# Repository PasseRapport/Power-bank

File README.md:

# Power-bank

The objective of this project is to upcycle an old flashlight into a usb C power bank while conserving the original look and functionnality.

It is based on the IP2368 charge controller wich allow for dual mode Power Delivery charging up to 100W. However this board is designed to to supply 45w max (5 Amps at 9 Volts).

<br>

<br>

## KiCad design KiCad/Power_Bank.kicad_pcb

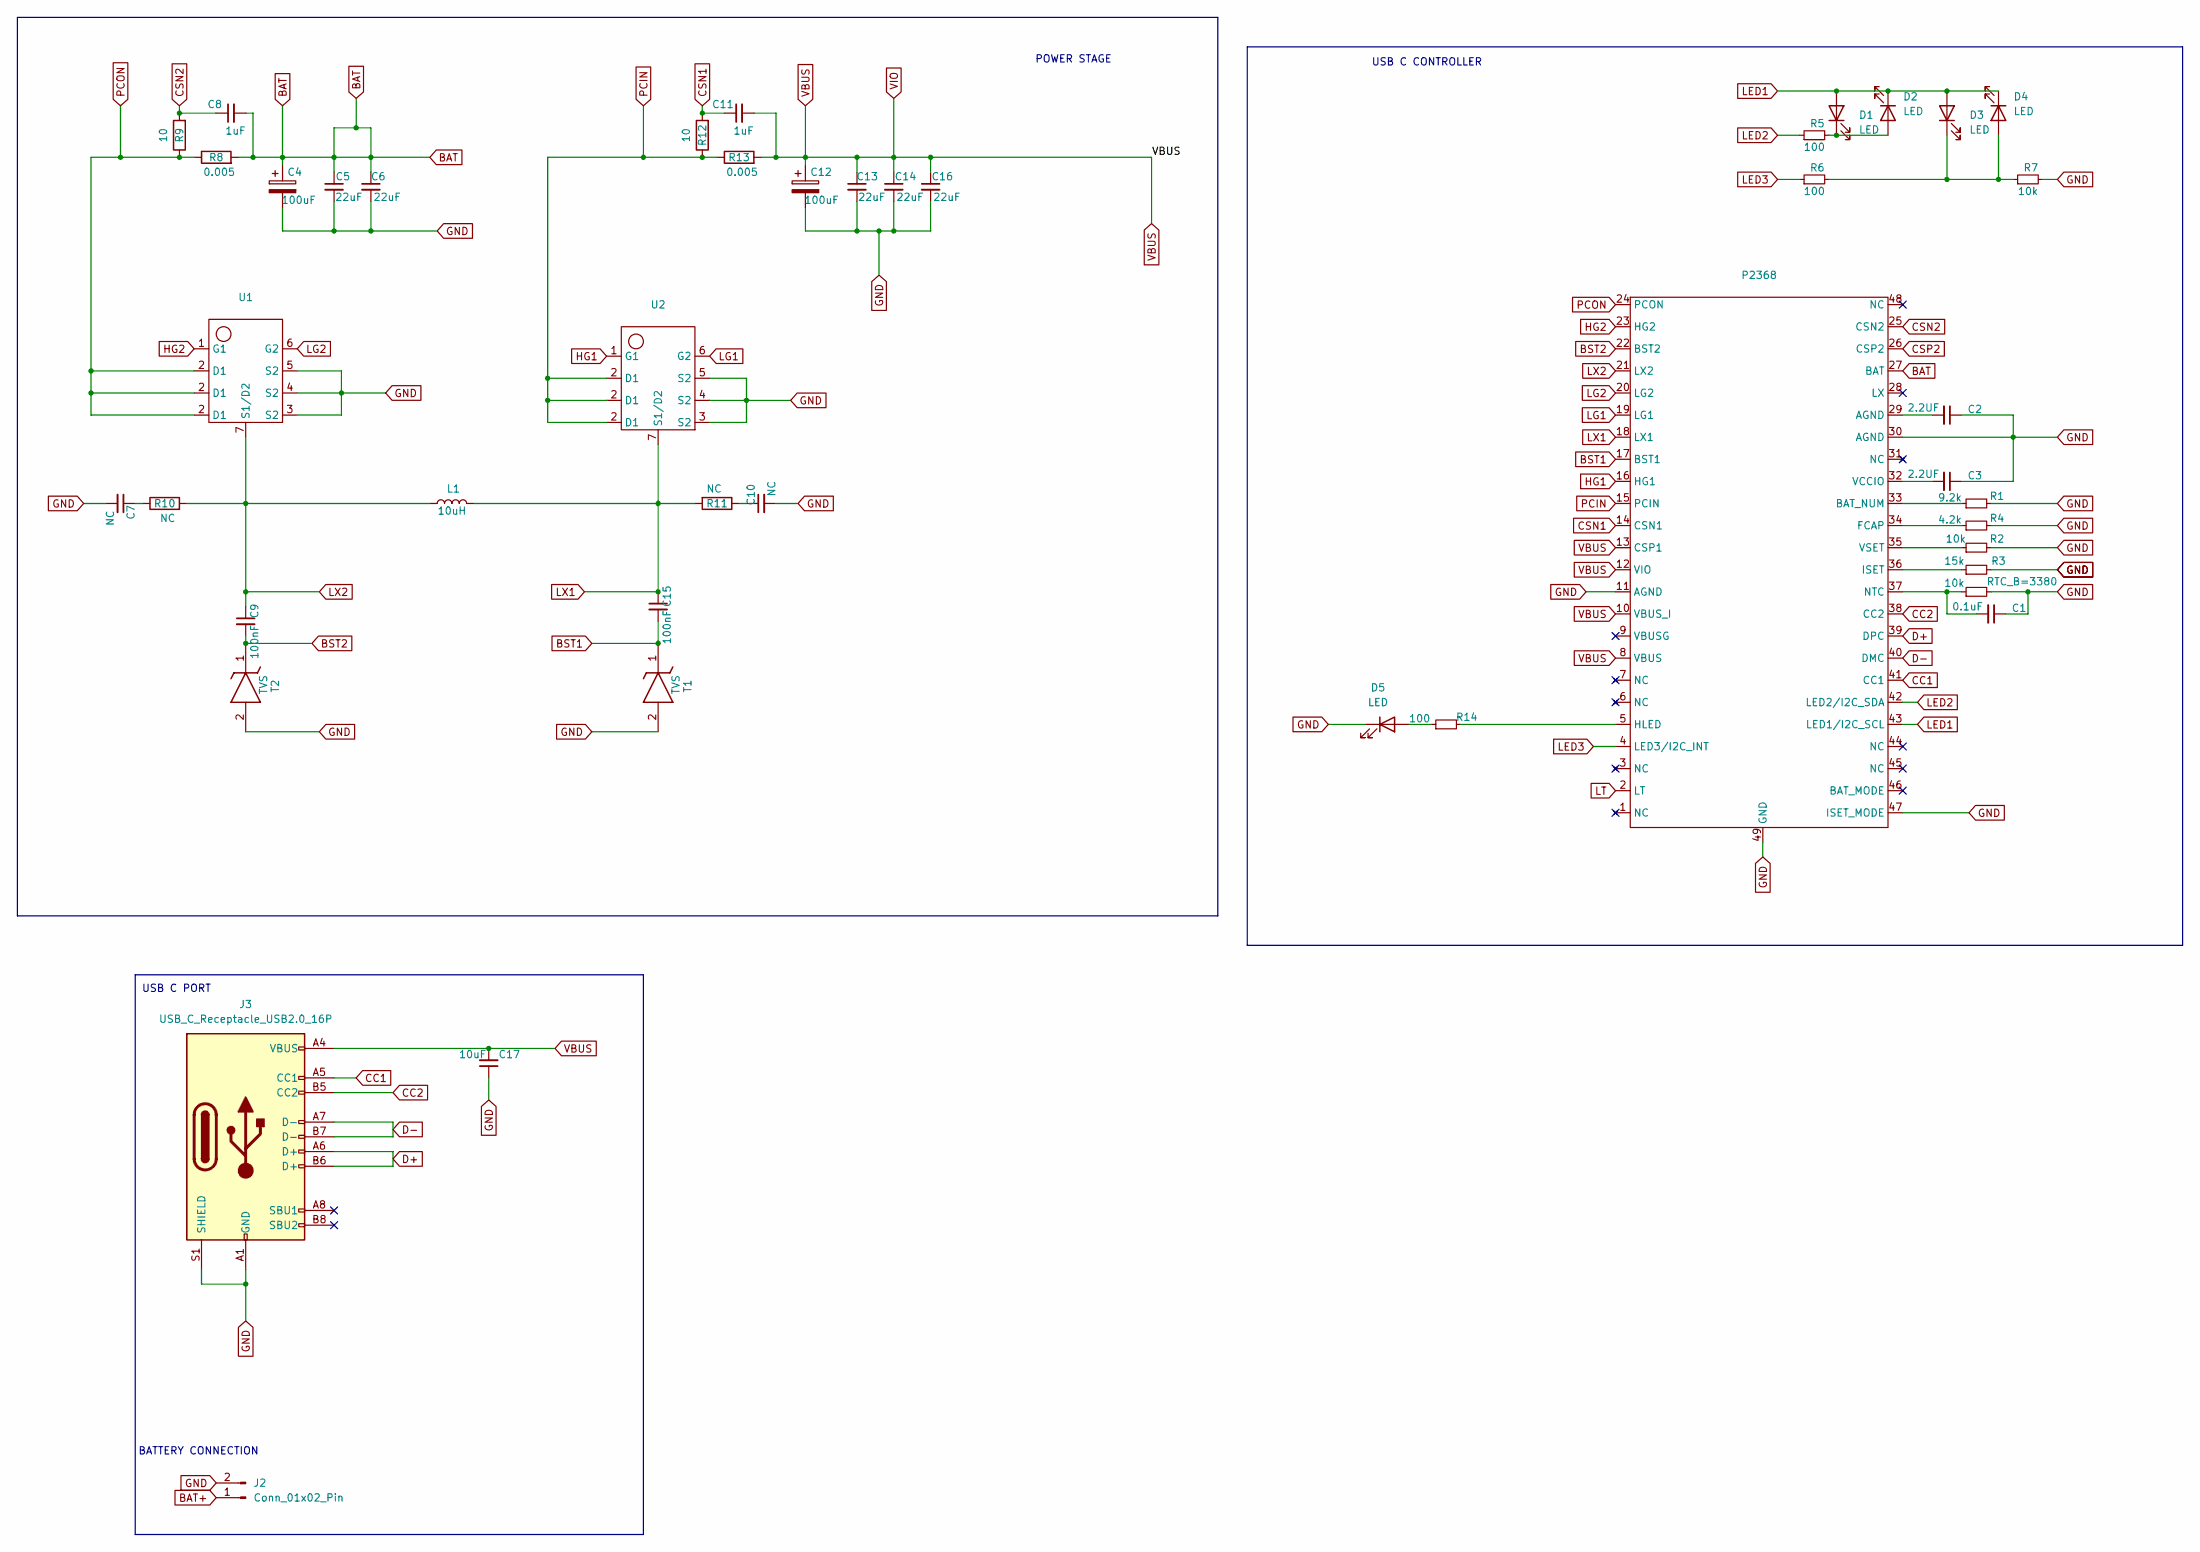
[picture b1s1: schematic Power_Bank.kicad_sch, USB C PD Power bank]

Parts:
C1: 0.1uF; C_0603_1608Metric
C2, C3: 2.2UF; C_0603_1608Metric
C4, C12: 100uF; CAPAE530X550N
C5, C6, C13, C14, C16: 22uF; C_0805_2012Metric
C7, C10: NC; C_0603_1608Metric
C8, C11: 1uF; C_0603_1608Metric
C9, C15: 100nF; C_0603_1608Metric
C17: 10uF; C_0805_2012Metric
D1, D2, D3, D4, D5: LED; D_0603_1608Metric
J2: Conn_01x02_Pin; Solder pad
J3: USB_C_Receptacle_USB2.0_16P; USB_C_Receptacle_XKB_U262-16XN-4BVC11
L1: 10uH; INDPM135125X650N
P2368: QFN-48-1EP_7x7mm_P0.5mm_EP5.7x5.7mm
R1: 9.2k; R_0603_1608Metric
R2, R7: 10k; R_0603_1608Metric
R3: 15k; R_0603_1608Metric
R4: 4.2k; R_0603_1608Metric
R5, R6, R14: 100; R_0603_1608Metric
R8, R13: 0.005; R_1206_3216Metric
R9, R12: 10; R_0603_1608Metric
R10, R11: NC; R_0603_1608Metric
RTC_B=3380: 10k; R_0603_1608Metric
T1, T2: TVS; DIOM4725X110N; Manufacturer_Part_Number PTVS30VP1UP; Mouser Part Number N/A
U1, U2: PDFN5060

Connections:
BST1: C15.2, P2368.17 (BST1), T1.1 (K); also elsewhere on the board
BST2: C9.2, P2368.22 (BST2), T2.1 (K); also elsewhere on the board
CC1: J3.A5 (CC1), P2368.41 (CC1); also elsewhere on the board
CC2: J3.B5 (CC2), P2368.38 (CC2); also elsewhere on the board
CSN1: C11.1, P2368.14 (CSN1), R12.2; also elsewhere on the board
CSN2: C8.1, P2368.25 (CSN2), R9.2; also elsewhere on the board
D+: J3.A6 (D+), J3.B6 (D+), P2368.39 (DPC); also elsewhere on the board
D-: J3.A7 (D-), J3.B7 (D-), P2368.40 (DMC); also elsewhere on the board
GND: C1.1, C2.1, C3.1, C4.2, C5.2, C6.2, C7.2, C10.2, C12.2, C13.2, C14.2, C16.2, C17.1, D5.1 (K), J2.2, J3.A1 (GND), J3.A12 (GND), J3.B1 (GND), J3.B12 (GND), J3.S1 (SHIELD), P2368.11 (AGND), P2368.30 (AGND), P2368.47 (ISET_MODE), P2368.49 (GND), R1.2, R2.2, R3.2, R4.2, R7.2, RTC_B=3380.2, T1.2 (A), T2.2 (A), U1.3 (S2), U1.4 (S2), U1.5 (S2), U2.3 (S2), U2.4 (S2), U2.5 (S2); also elsewhere on the board
HG1: P2368.16 (HG1), U2.1 (G1); also elsewhere on the board
HG2: P2368.23 (HG2), U1.1 (G1); also elsewhere on the board
LED1: D1.2 (A), D2.1 (K), D3.2 (A), D4.1 (K), P2368.43 (LED1/I2C_SCL); also elsewhere on the board
LED2: P2368.42 (LED2/I2C_SDA), R5.1; also elsewhere on the board
LED3: P2368.4 (LED3/I2C_INT), R6.1; also elsewhere on the board
LG1: P2368.19 (LG1), U2.6 (G2); also elsewhere on the board
LG2: P2368.20 (LG2), U1.6 (G2); also elsewhere on the board
LX1: C15.1, L1.2, P2368.18 (LX1), R11.2, U2.7 (S1/D2); also elsewhere on the board
LX2: C9.1, L1.1, P2368.21 (LX2), R10.2, U1.7 (S1/D2); also elsewhere on the board
unnamed 19: C2.2, P2368.29 (AGND); also elsewhere on the board
unnamed: C7.1, R10.1
unnamed: C10.1, R11.1
unnamed: D1.1 (K), D2.2 (A), R5.2
unnamed: D3.1 (K), D4.2 (A), R6.2, R7.1
unnamed: D5.2 (A), R14.1
unnamed 25: P2368.33 (BAT_NUM), R1.1; also elsewhere on the board
unnamed 26: P2368.34 (FCAP), R4.1; also elsewhere on the board
unnamed 27: P2368.5 (HLED), R14.2; also elsewhere on the board
unnamed 28: P2368.36 (ISET), R3.1; also elsewhere on the board
unnamed 29: C1.2, P2368.37 (NTC), RTC_B=3380.1; also elsewhere on the board
unnamed 30: C3.2, P2368.32 (VCCIO); also elsewhere on the board
unnamed 31: P2368.35 (VSET), R2.1; also elsewhere on the board
PCIN: P2368.15 (PCIN), R12.1, R13.1, U2.2 (D1); also elsewhere on the board
PCON: P2368.24 (PCON), R8.1, R9.1, U1.2 (D1); also elsewhere on the board
VBUS: C11.2, C12.1, C13.1, C14.1, C16.1, C17.2, J3.A4 (VBUS), J3.A9 (VBUS), J3.B4 (VBUS), J3.B9 (VBUS), P2368.8 (VBUS), P2368.10 (VBUS_I), P2368.12 (VIO), P2368.13 (CSP1), R13.2; also elsewhere on the board

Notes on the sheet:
BATTERY CONNECTION
USB C CONTROLLER
USB C PORT
POWER STAGE

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
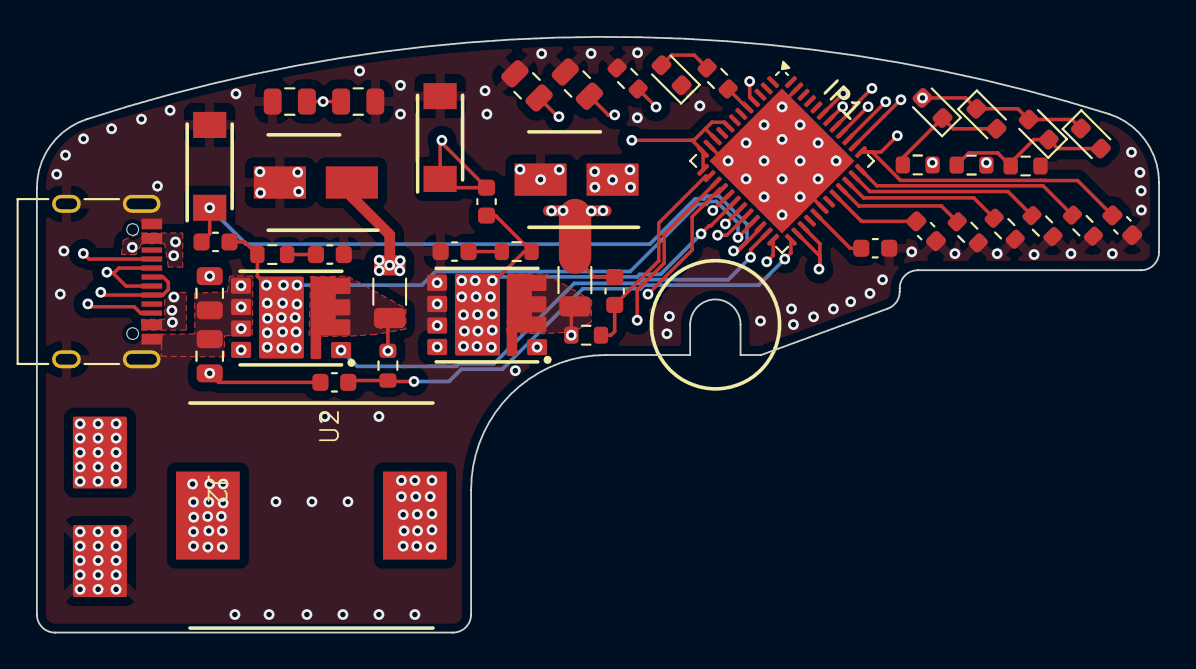
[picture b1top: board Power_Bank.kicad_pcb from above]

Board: 4 copper layers, 62.3 x 33.1 mm, 45 parts (0 on the bottom side), 35 nets.

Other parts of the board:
IP1: QFN-48-1EP_7x7mm_P0.5mm_EP5.7x5.7mm

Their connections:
BST1: IP1.17 (BST1); also elsewhere on the board
BST2: IP1.22 (BST2); also elsewhere on the board
CC1: IP1.41 (CC1); also elsewhere on the board
CC2: IP1.38 (CC2); also elsewhere on the board
CSN1: IP1.14 (CSN1); also elsewhere on the board
CSN2: IP1.25 (CSN2); also elsewhere on the board
D+: IP1.39 (DPC); also elsewhere on the board
D-: IP1.40 (DMC); also elsewhere on the board
GND: IP1.11 (AGND), IP1.30 (AGND), IP1.47 (ISET_MODE), IP1.49 (GND); also elsewhere on the board
HG1: IP1.16 (HG1); also elsewhere on the board
HG2: IP1.23 (HG2); also elsewhere on the board
LED1: IP1.43 (LED1/I2C_SCL); also elsewhere on the board
LED2: IP1.42 (LED2/I2C_SDA); also elsewhere on the board
LED3: IP1.4 (LED3/I2C_INT); also elsewhere on the board
LG1: IP1.19 (LG1); also elsewhere on the board
LG2: IP1.20 (LG2); also elsewhere on the board
LX1: IP1.18 (LX1); also elsewhere on the board
LX2: IP1.21 (LX2); also elsewhere on the board
unnamed 19: IP1.29 (AGND); also elsewhere on the board
unnamed 25: IP1.33 (BAT_NUM); also elsewhere on the board
unnamed 26: IP1.34 (FCAP); also elsewhere on the board
unnamed 27: IP1.5 (HLED); also elsewhere on the board
unnamed 28: IP1.36 (ISET); also elsewhere on the board
unnamed 29: IP1.37 (NTC); also elsewhere on the board
unnamed 30: IP1.32 (VCCIO); also elsewhere on the board
unnamed 31: IP1.35 (VSET); also elsewhere on the board
PCIN: IP1.15 (PCIN); also elsewhere on the board
PCON: IP1.24 (PCON); also elsewhere on the board
VBUS: IP1.8 (VBUS), IP1.10 (VBUS_I), IP1.12 (VIO), IP1.13 (CSP1); also elsewhere on the board

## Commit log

2026-01-20 Readme correction
2026-01-20 Readme update and datasheet
